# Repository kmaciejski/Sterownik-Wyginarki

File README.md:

# Projekt sterownika wyginarki do profili stalowych

## Dane Techniczne
- Low cost MCU STM32F030F4P6
- Ekran LCD alfanumeryczny podłączony do magistrali I2C
- Podłączenie klawiatury 12 przyciskowej zrealizowane na 2 rejstrach 74HC166N
- Zewnętrzna pamięć EEPROM na płytce PCB do zapamiętywania ustawień podłączona do magistrali I2C
- Podłączony enkoder z linią Zerującą obsługiwany na przerwaniach
- Wyprowadzone wyjścia przekaźnikowe do sterowania stycznikami silnika i wbudowane przekaźniki na płytce PCB
- Zasilanie zewnętrzne 12V i wbudowane regulatory napięcia dla logiki na płytce PCB

## Możliwości
- Funkcja Automatycznego startu maszyny
- Funkcja Autocofania 
- Funkcja pamięci nastaw (8 różnych nastaw do zapamiętania M1-M8)
- Wielopoziomowe menu
- Zaawansowana obsługa przycisków na klawiaturze m.in. przytrzymanie i autorepetycja

## Działający prototyp

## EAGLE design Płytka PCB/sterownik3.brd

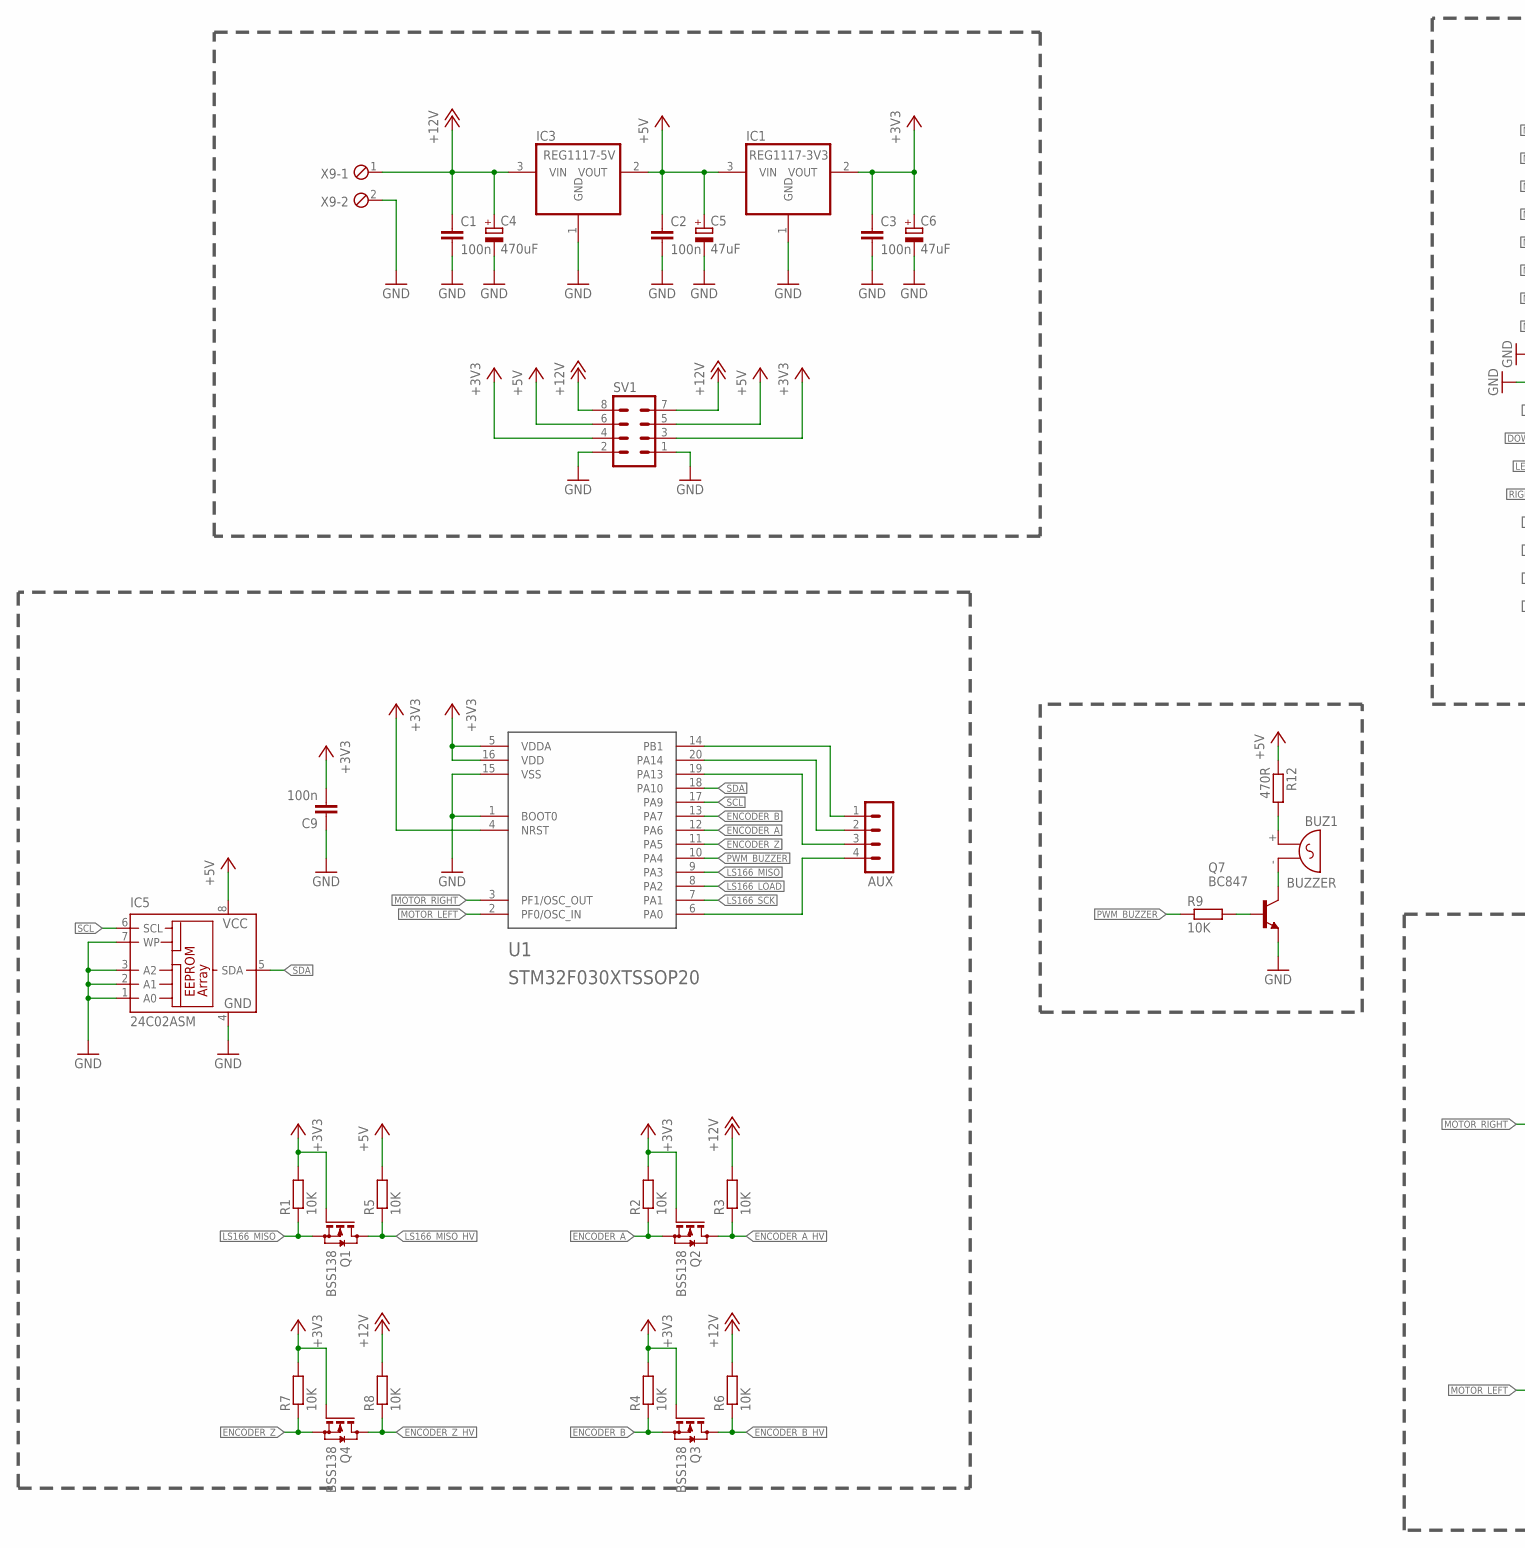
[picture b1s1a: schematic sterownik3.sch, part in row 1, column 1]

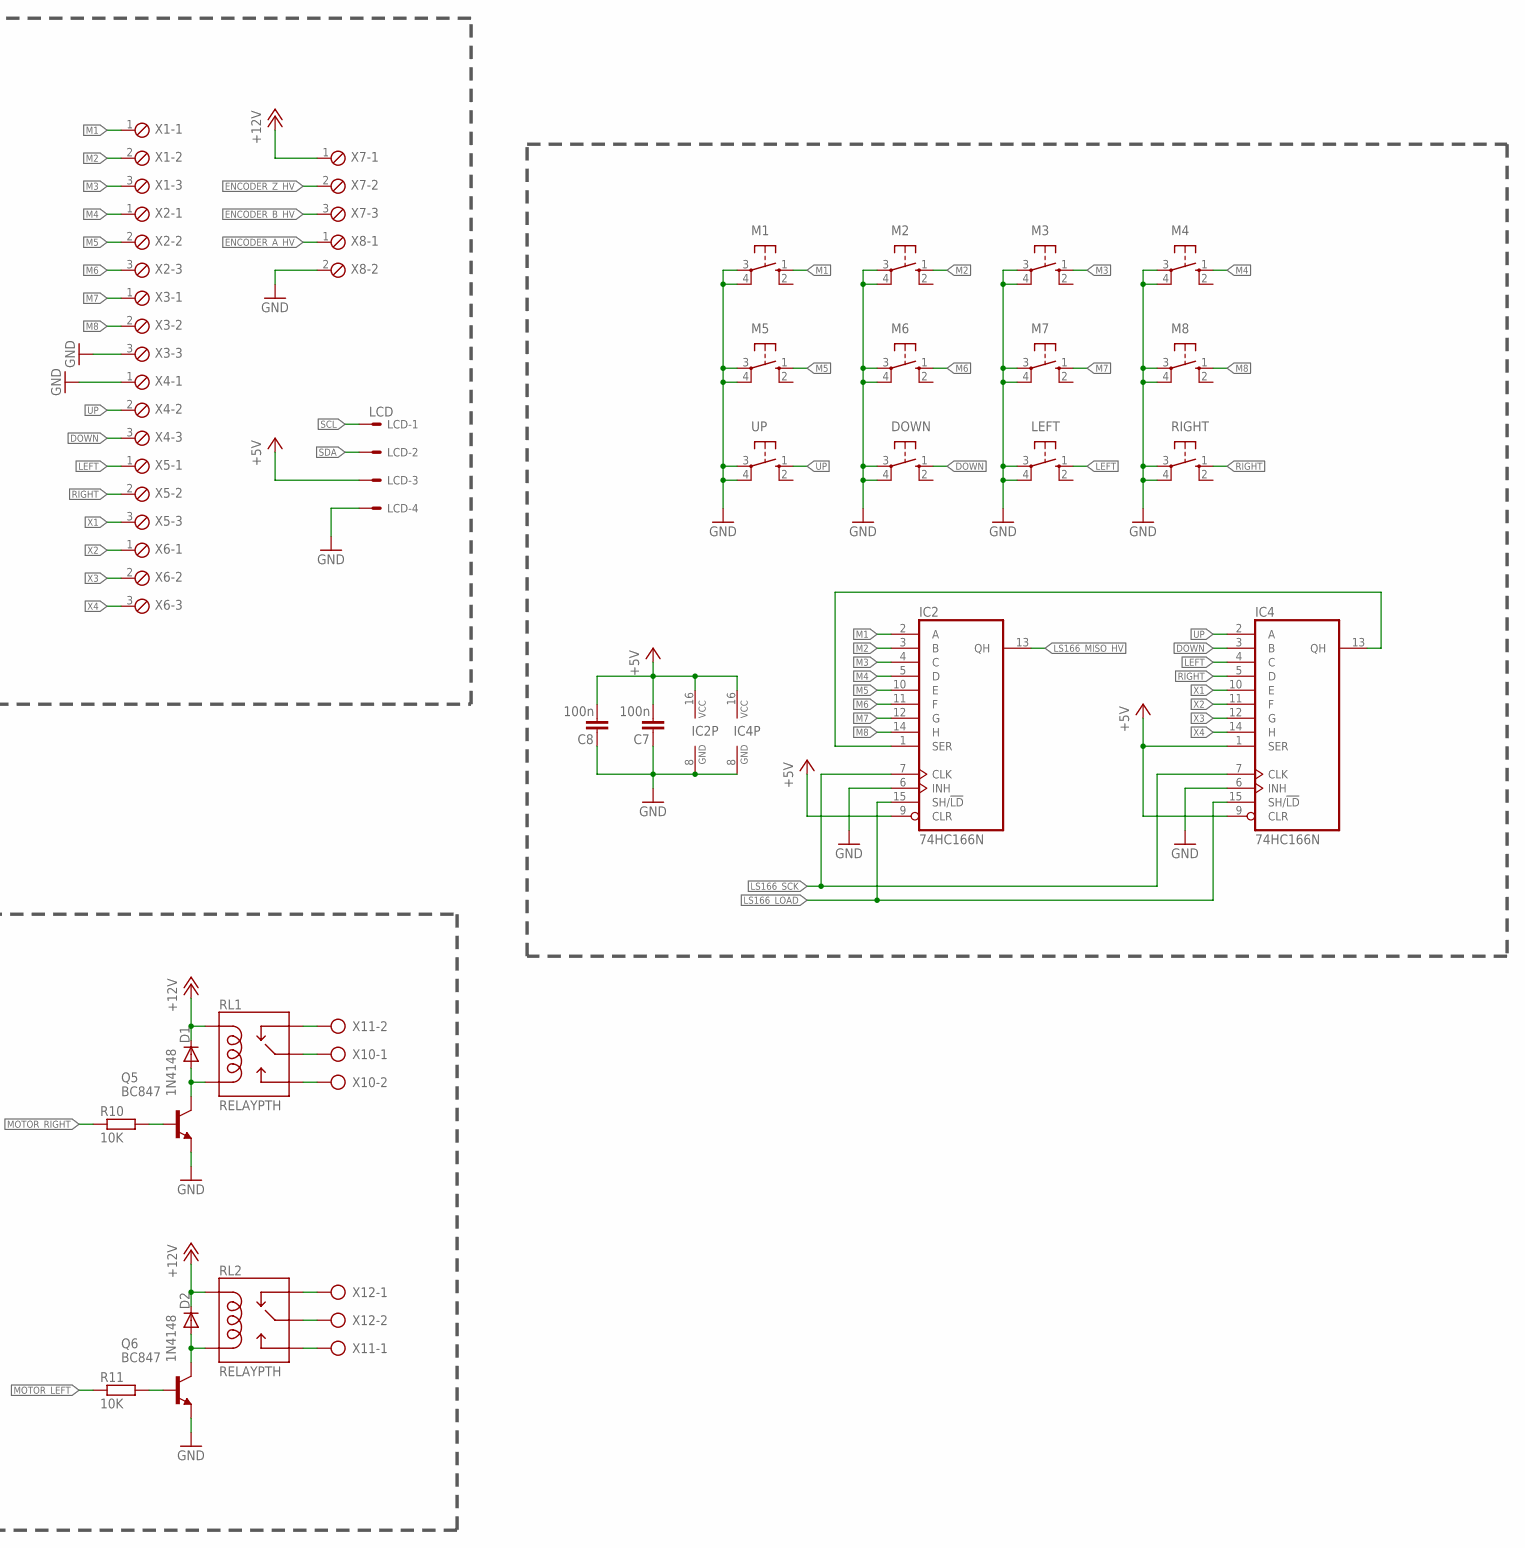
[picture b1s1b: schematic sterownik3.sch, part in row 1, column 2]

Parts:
AUX: MA04-1
BUZ1: BUZZER; F/QMX
C1, C2, C3, C7, C8, C9: 100n; C0805
C4: 470uF; E5-8,5
C5, C6: 47uF; E5-6
D1, D2: 1N4148; DO35-7
DOWN: 10-XX; B3F-10XX
IC1: REG1117-3V3; SOT223
IC2, IC4: 74HC166N; DIL16
IC3: REG1117-5V; SOT223
IC5: 24C02ASM; SO-08M
LCD: LCD; 6410-04
LEFT: 10-XX; B3F-10XX
M1, M2, M3, M4, M5, M6, M7, M8: 10-XX; B3F-10XX
Q1, Q2, Q3, Q4: BSS138; SOT23
Q5, Q6, Q7: BC847; SOT23
R1, R2, R3, R4, R5, R6, R7, R8, R9, R10, R11: 10K; R0805
R12: 470R; R0805
RIGHT: 10-XX; B3F-10XX
RL1, RL2: RELAYPTH; SRD-05VDC-SL-C
SV1: MA04-2
U1: STM32F030XTSSOP20; TSSOP-20
UP: 10-XX; B3F-10XX
X1, X2, X3, X4, X5, X6, X7: MPT3; 3POL254
X8, X9: MPT2; 2POL254
X10, X11, X12: AK500/2

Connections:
+3V3: C3.1, C6.+, C9.2, IC1.2 (VOUT), Q1.1 (G), Q2.1 (G), Q3.1 (G), Q4.1 (G), R1.2, R2.2, R4.2, R7.2, SV1.3, SV1.4, U1.4 (NRST), U1.5 (VDDA), U1.16 (VDD)
+5V: C2.1, C5.+, C7.1, C8.1, IC1.3 (VIN), IC2.9 (CLR), IC2.16 (VCC), IC3.2 (VOUT), IC4.1 (SER), IC4.9 (CLR), IC4.16 (VCC), IC5.8 (VCC), LCD.3, R5.2, R12.1, SV1.5, SV1.6
+12V: C1.1, C4.+, D1.C, D2.C, IC3.3 (VIN), R3.2, R6.2, R8.2, RL1.COIL1, RL2.COIL1, SV1.7, SV1.8, X7.1, X9.1
DOWN: DOWN.1 (S), IC4.3 (B), X4.3
ENCODER_A: Q2.2 (S), R2.1, U1.12 (PA6)
ENCODER_A_HV: Q2.3 (D), R3.1, X8.1
ENCODER_B: Q3.2 (S), R4.1, U1.13 (PA7)
ENCODER_B_HV: Q3.3 (D), R6.1, X7.3
ENCODER_Z: Q4.2 (S), R7.1, U1.11 (PA5)
ENCODER_Z_HV: Q4.3 (D), R8.1, X7.2
GND: C1.2, C2.2, C3.2, C4.-, C5.-, C6.-, C7.2, C8.2, C9.1, DOWN.3, DOWN.4 (P1), IC1.1 (GND), IC2.6 (INH), IC2.8 (GND), IC3.1 (GND), IC4.6 (INH), IC4.8 (GND), IC5.1 (A0), IC5.2 (A1), IC5.3 (A2), IC5.4 (GND), IC5.7 (WP), LCD.4, LEFT.3, LEFT.4 (P1), M1.3, M1.4 (P1), M2.3, M2.4 (P1), M3.3, M3.4 (P1), M4.3, M4.4 (P1), M5.3, M5.4 (P1), M6.3, M6.4 (P1), M7.3, M7.4 (P1), M8.3, M8.4 (P1), Q5.2 (E), Q6.2 (E), Q7.2 (E), RIGHT.3, RIGHT.4 (P1), SV1.1, SV1.2, U1.1 (BOOT0), U1.15 (VSS), UP.3, UP.4 (P1), X3.3, X4.1, X8.2, X9.2
LEFT: IC4.4 (C), LEFT.1 (S), X5.1
LS166_LOAD: IC2.15 (SH/!LD), IC4.15 (SH/!LD), U1.8 (PA2)
LS166_MISO: Q1.2 (S), R1.1, U1.9 (PA3)
LS166_MISO_HV: IC2.13 (QH), Q1.3 (D), R5.1
LS166_SCK: IC2.7 (CLK), IC4.7 (CLK), U1.7 (PA1)
M1: IC2.2 (A), M1.1 (S), X1.1
M2: IC2.3 (B), M2.1 (S), X1.2
M3: IC2.4 (C), M3.1 (S), X1.3
M4: IC2.5 (D), M4.1 (S), X2.1
M5: IC2.10 (E), M5.1 (S), X2.2
M6: IC2.11 (F), M6.1 (S), X2.3
M7: IC2.12 (G), M7.1 (S), X3.1
M8: IC2.14 (H), M8.1 (S), X3.2
MOTOR_LEFT: R11.1, U1.2 (PF0/OSC_IN)
MOTOR_RIGHT: R10.1, U1.3 (PF1/OSC_OUT)
unnamed: AUX.3, U1.19 (PA13)
unnamed: AUX.2, U1.20 (PA14)
unnamed: AUX.1, U1.14 (PB1)
unnamed: AUX.4, U1.6 (PA0)
unnamed: BUZ1.- (1), Q7.3 (C)
unnamed: BUZ1.+ (2), R12.2
unnamed: Q7.1 (B), R9.2
unnamed: Q6.1 (B), R11.2
unnamed: Q5.1 (B), R10.2
unnamed: D1.A, Q5.3 (C), RL1.COIL0
unnamed: D2.A, Q6.3 (C), RL2.COIL0
unnamed: RL2.SWCLOSED (SWCLOSE), X12.1
unnamed: RL1.SWCOMMON, X10.1
unnamed: RL2.SWOPEN, X11.1
unnamed: RL1.SWCLOSED (SWCLOSE), X11.2
unnamed: RL2.SWCOMMON, X12.2
unnamed: RL1.SWOPEN, X10.2
unnamed: IC2.1 (SER), IC4.13 (QH)
PWM_BUZZER: R9.1, U1.10 (PA4)
RIGHT: IC4.5 (D), RIGHT.1 (S), X5.2
SCL: IC5.6 (SCL), LCD.1, U1.17 (PA9)
SDA: IC5.5 (SDA), LCD.2, U1.18 (PA10)
UP: IC4.2 (A), UP.1 (S), X4.2
X1: IC4.10 (E), X5.3
X2: IC4.11 (F), X6.1
X3: IC4.12 (G), X6.2
X4: IC4.14 (H), X6.3

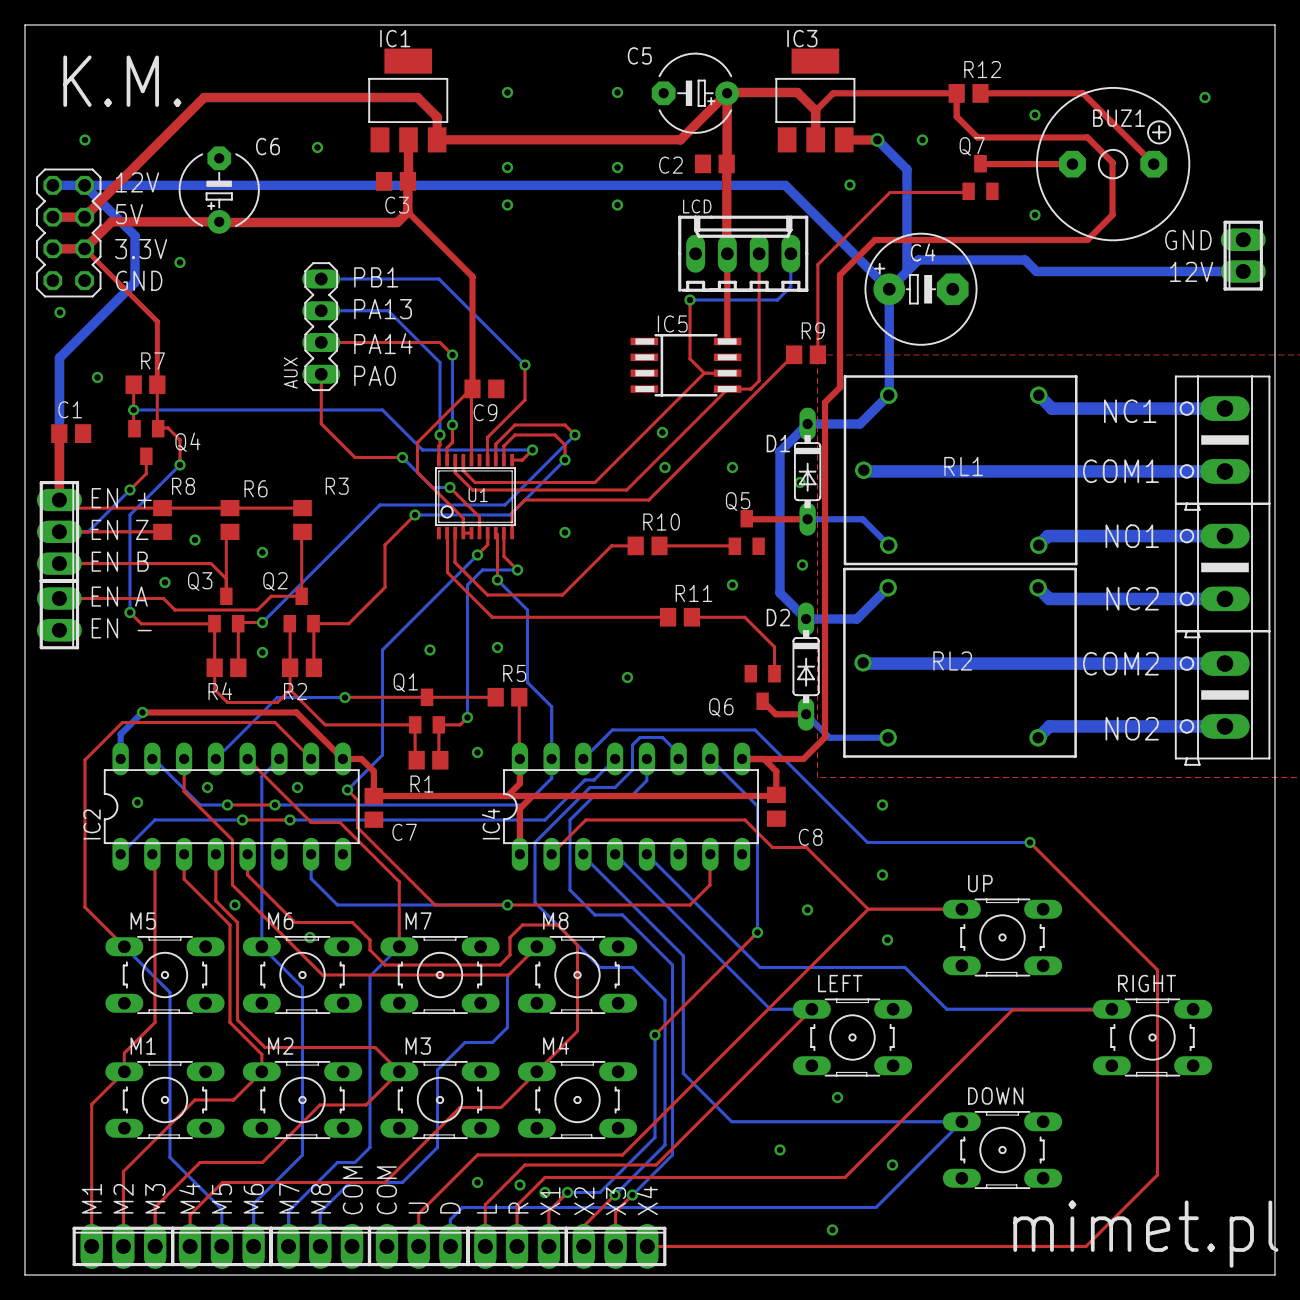
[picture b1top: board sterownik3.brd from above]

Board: 2 copper layers, 100.0 x 100.0 mm, 66 parts (0 on the bottom side), 53 nets.

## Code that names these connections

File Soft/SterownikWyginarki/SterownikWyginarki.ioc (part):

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Mcu.Name=STM32F030F4Px
Mcu.Package=TSSOP20
Mcu.UserName=STM32F030F4Px
PA1.GPIOParameters=GPIO_PuPd,GPIO_Label
PA1.GPIO_Label=LS166_SCK
PA1.GPIO_PuPd=GPIO_PULLDOWN
PA1.Signal=GPIO_Output
PA10.Mode=I2C
PA10.Signal=I2C1_SDA
PA2.GPIOParameters=GPIO_PuPd,GPIO_Label
PA2.GPIO_Label=LS166_LOAD
PA2.GPIO_PuPd=GPIO_PULLDOWN
PA2.Signal=GPIO_Output
PA3.GPIOParameters=GPIO_PuPd,GPIO_Label
PA3.GPIO_Label=LS166_MISO
PA3.GPIO_PuPd=GPIO_PULLDOWN
PA3.Signal=GPIO_Input
PA4.GPIOParameters=GPIO_Label
PA4.GPIO_Label=PWM_BUZZER
PA4.Signal=S_TIM14_CH1
PA5.GPIOParameters=GPIO_PuPd,GPIO_Label,GPIO_ModeDefaultEXTI
PA5.GPIO_Label=ENCODER_Z
PA5.GPIO_ModeDefaultEXTI=GPIO_MODE_IT_RISING
PA5.GPIO_PuPd=GPIO_NOPULL
PA5.Signal=GPXTI5
PA6.GPIOParameters=GPIO_Label
PA6.GPIO_Label=ENCODER_A
PA6.Signal=S_TIM3_CH1
PA7.GPIOParameters=GPIO_Label
PA7.GPIO_Label=ENCODER_B
PA7.Signal=S_TIM3_CH2
PA9.Mode=I2C
PA9.Signal=I2C1_SCL
PF0-OSC_IN.GPIOParameters=GPIO_Label
PF0-OSC_IN.GPIO_Label=MOTOR_LEFT
PF0-OSC_IN.Signal=GPIO_Output
PF1-OSC_OUT.GPIOParameters=GPIO_Label
PF1-OSC_OUT.GPIO_Label=MOTOR_RIGHT
PF1-OSC_OUT.Signal=GPIO_Output
RCC.SYSCLKFreq_VALUE=48000000
RCC.SYSCLKSource=RCC_SYSCLKSOURCE_PLLCLK
board=SterownikWyginarki
